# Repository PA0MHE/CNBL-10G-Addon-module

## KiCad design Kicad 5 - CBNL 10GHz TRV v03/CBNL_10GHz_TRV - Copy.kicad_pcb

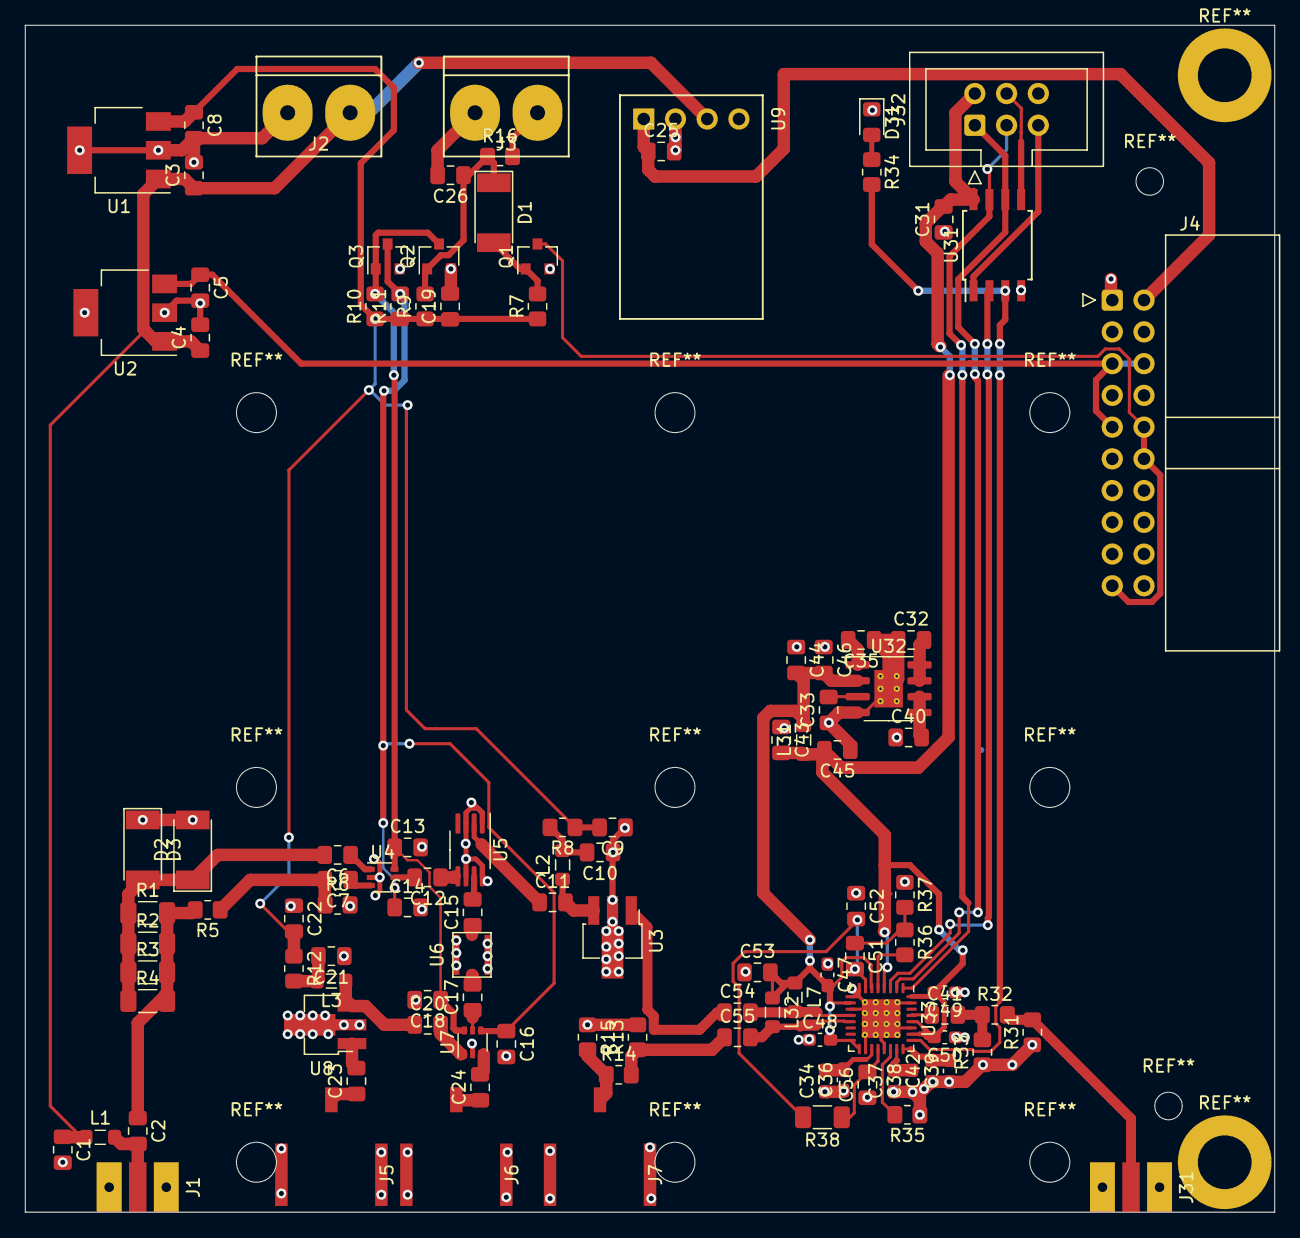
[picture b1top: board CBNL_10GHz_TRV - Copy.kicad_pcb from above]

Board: 2 copper layers, 100.0 x 95.0 mm, 110 parts (0 on the bottom side), 62 nets.

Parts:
C1, C2, C6, C7, C9, C10, C12, C16, C18, C19, C21, C22, C46, C53: 100p; C_0805_2012Metric_Pad1.18x1.45mm_HandSolder
C3, C25, C32, C43, C44: 10u; C_0805_2012Metric_Pad1.18x1.45mm_HandSolder
C4, C5, C8, C26: 10n; C_0805_2012Metric_Pad1.18x1.45mm_HandSolder
C11, C15, C17, C20, C23, C24, C54, C55: 10p; C_0805_2012Metric_Pad1.18x1.45mm_HandSolder
C13, C14, C41: 1n; C_0805_2012Metric_Pad1.18x1.45mm_HandSolder
C31: 100n; C_0805_2012Metric_Pad1.18x1.45mm_HandSolder
C33, C35, C40: 1u; C_0805_2012Metric_Pad1.18x1.45mm_HandSolder
C34, C37, C39: 100n; C_0603_1608Metric_Pad1.08x0.95mm_HandSolder
C36, C38, C42: 10p; C_0603_1608Metric_Pad1.08x0.95mm_HandSolder
C45: 120p; C_0805_2012Metric_Pad1.18x1.45mm_HandSolder
C47, C48, C49: 100p; C_0603_1608Metric_Pad1.08x0.95mm_HandSolder
C50: 10n; C_0603_1608Metric_Pad1.08x0.95mm_HandSolder
C51: 39n; C_0805_2012Metric_Pad1.18x1.45mm_HandSolder
C52: 2n7; C_0805_2012Metric_Pad1.18x1.45mm_HandSolder
C56: 1n2; C_0805_2012Metric_Pad1.18x1.45mm_HandSolder
D1, D2, D3: D; D_MELF
D31: LED; LED_0805_2012Metric_Pad1.15x1.40mm_HandSolder
J1: 432 RX/TX; SMA_side_PCB
J2: 12V; KF301-2P
J3: PTT; KF301-2P
J4: Conn_02x10_Top_Bottom; IDC-Header_2x10_P2.54mm_Horizontal_MH
J5: RX in 2419.2 MHz; SMB
J6: TX out 2419.2 MHz; SMB
J7: LO/3 1987.2MHz; SMB
J31: SMA 10MHz; SMA_side_PCB
J32: ICPC; IDC-Header_2x03_P2.54mm_Vertical
L1: 100n; L_0805_2012Metric_Pad1.05x1.20mm_HandSolder
L2, L3: 15n; L_0805_2012Metric_Pad1.05x1.20mm_HandSolder
L7, L32: 3n9; L_0805_2012Metric_Pad1.05x1.20mm_HandSolder
L31: 100u; L_0805_2012Metric_Pad1.05x1.20mm_HandSolder
Q1, Q2, Q3: BC849; SOT-23
R1, R2, R3, R4: 200R; R_1206_3216Metric_Pad1.30x1.75mm_HandSolder
R5, R16: 1K; R_0805_2012Metric_Pad1.20x1.40mm_HandSolder
R6: 50R; R_0805_2012Metric_Pad1.20x1.40mm_HandSolder
R7: 47K; R_0805_2012Metric_Pad1.20x1.40mm_HandSolder
R8, R14: 10; R_0805_2012Metric_Pad1.20x1.40mm_HandSolder
R9, R10, R11: 22K; R_0805_2012Metric_Pad1.20x1.40mm_HandSolder
R12: 20; R_0805_2012Metric_Pad1.20x1.40mm_HandSolder
R13, R15: 470; R_0805_2012Metric_Pad1.20x1.40mm_HandSolder
R31, R32, R33: R; R_0805_2012Metric_Pad1.20x1.40mm_HandSolder
R34: 2K2; R_0805_2012Metric_Pad1.20x1.40mm_HandSolder
R35: 5K1; R_0805_2012Metric_Pad1.20x1.40mm_HandSolder
R36, R37: 720; R_0805_2012Metric_Pad1.20x1.40mm_HandSolder
R38: 680; R_1206_3216Metric_Pad1.30x1.75mm_HandSolder
U1: L7805; SOT-223-3_TabPin2
U2: L7808; SOT-223-3_TabPin2
U3: SBB3089Z; SOT-89-3_Handsoldering
U4, U7: AS179-92LF; SOT-363_SC-70-6
U5: HMC213B; MSOP-8_3x3mm_P0.65mm
U6: LFSN25C16C2450; LFSN25N
U8: PGA103+; SOT-89-3_Handsoldering
U9: MiniBuck
U31: ATtiny85-20SU; SOIJ-8_5.3x5.3mm_P1.27mm
U32: ADM7150DZ-3V3; SOIC-8-1EP_3.9x4.9mm_P1.27mm_EP2.29x3mm_ThermalVias
U33: ADF4351; LFCSP-32-1EP_5x5mm_P0.5mm_EP3.1x3.1mm_ThermalVias

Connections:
12V: C32.2, U32.7, U32.8
+3.3VA: C44.2, C46.2, C47.2, C48.2, C53.2, L7.1, L31.2, L32.1, U32.2, U33.6, U33.10, U33.16, U33.17
+3V3: C31.2, C43.2, C45.2, C49.2, C50.2, J32.2, L31.1, U31.8, U33.4, U33.26, U33.28, U33.32
+5V: C8.1, C9.2, C19.1, C22.2, R7.1, R8.1, R9.1, R10.1, R11.1, R12.1, U1.3
+6.5V: C25.1, J4.11, U9.1
+8V: C5.1, J4.3, J4.5, J4.13, U2.3
GNDREF: C1.2, C3.2, C4.2, C5.2, C8.2, C9.1, C10.1, C13.2, C14.2, C16.2, C18.2, C19.2, C21.1, C22.1, C25.2, C26.2, C31.1, C32.1, C33.1, C34.1, C35.1, C36.1, C37.1, C38.1, C39.1, C40.1, C42.1, C43.1, C44.1, C45.1, C46.1, C47.1, C48.1, C49.1, C50.1, C52.1, C53.1, C56.1, D2.2, D3.1, D31.1, J1.2, J2.2, J3.2, J4.1, J4.2, J4.4, J4.7, J4.12, J4.14, J5.2, J6.2, J7.2, J31.2, J32.6, Q1.2, Q2.2, Q3.2, R6.2, R13.2, R15.1, R31.1, R33.1, R35.1, R37.1, U1.2, U2.2, U3.2, U4.2, U5.1, U5.3, U5.6, U5.8, U6.3, U6.4, U7.2, U8.2, U9.2, U31.4, U32.4, U32.9, U33.8, U33.9, U33.11, U33.18, U33.21, U33.27, U33.31, U33.33
LO_A: C54.1, U3.1
LO_B: C55.1, R13.1, R14.2
unnamed: C1.1, C3.1, C4.1, J2.1, L1.1, U1.1, U2.1, U9.3
unnamed: C2.1, R1.2, R2.2, R3.2, R4.2, R5.2
unnamed: C2.2, J1.1, L1.2
unnamed: C6.1, U4.1
unnamed: C6.2, D2.1, D3.2, R1.1, R2.1, R3.1, R4.1
unnamed: C7.1, U4.3
unnamed: C7.2, R5.1, R6.1
unnamed: C10.2, L2.2, R8.2
unnamed: C11.1, U5.2
unnamed: C11.2, L2.1, U3.3
unnamed: C12.1, U5.5
unnamed: C12.2, U4.5
unnamed: C13.1, C18.1, Q2.3, Q3.1, R10.2, U4.6, U7.6
unnamed: C14.1, C16.1, Q3.3, R11.2, U4.4, U7.4
unnamed: C15.1, U6.1
unnamed: C15.2, U5.7
unnamed: C17.1, U7.5
unnamed: C17.2, U6.2
unnamed: C20.1, L3.1, U8.3
unnamed: C20.2, U7.1
unnamed: C21.2, L3.2, R12.2
unnamed: C23.1, J5.1
unnamed: C23.2, U8.1
unnamed: C24.1, J6.1
unnamed: C24.2, U7.3
unnamed: C26.1, D1.1, Q2.1, R9.2, R16.1
unnamed: C33.2, U32.3
unnamed: C34.2, C36.2, U33.19
unnamed: C35.2, U32.1
unnamed: C37.2, C38.2, U33.23
unnamed: C39.2, C42.2, U33.24
unnamed: C40.2, U32.5, U32.6
unnamed: C41.1, U33.29
unnamed: C41.2, R32.1, R33.2
unnamed: C51.1, R36.1, R37.2
unnamed: C51.2, C52.2, R38.2, U33.7
unnamed: C54.2, L7.2, U33.12
unnamed: C55.2, L32.2, U33.13
unnamed: C56.2, R38.1, U33.20
unnamed: D1.2, Q1.1, R7.2
unnamed: D31.2, R34.1
unnamed: J3.1, R16.2
unnamed: J4.10, J4.15, J4.16, Q1.3
unnamed: J7.1, R14.1, R15.2
unnamed: J31.1, R31.2, R32.2
unnamed: J32.1, U31.6, U33.2
unnamed: J32.3, U31.7, U33.1
unnamed: J32.4, U31.5
unnamed: J32.5, U31.1
unnamed: R34.2, U31.3, U33.25
unnamed: R35.2, U33.22
unnamed: R36.2, U33.5
unnamed: U31.2, U33.3

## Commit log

2022-08-22 Added Kicad files
